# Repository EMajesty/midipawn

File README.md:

# midipawn

MIDI-controlled relay switcher built on the Raspberry Pi Pico (RP2040). Accepts MIDI over USB and TRS (GPIO 9). Controls 10 bypass relays via GPIO 10-19.

## MIDI interface

The device accepts messages on both USB MIDI and serial MIDI (TRS input on GPIO 9). Default MIDI channel is **6**.

### Relay control

Relay states are set via two CC messages. Each CC value is a 5-bit bitmask where bit 0 is the lowest-numbered relay in the group.

| CC  | Bit 0 | Bit 1 | Bit 2 | Bit 3 | Bit 4 |
|-----|-------|-------|-------|-------|-------|
| 80  | Relay 1 (GPIO 10) | Relay 2 (GPIO 11) | Relay 3 (GPIO 12) | Relay 4 (GPIO 13) | Relay 5 (GPIO 14) |
| 81  | Relay 6 (GPIO 15) | Relay 7 (GPIO 16) | Relay 8 (GPIO 17) | Relay 9 (GPIO 18) | Relay 10 (GPIO 19) |

Example: sending CC 80 with value `0x15` (binary `10101`) activates relays 1, 3, 5 and deactivates relays 2, 4.

### Channel configuration

The MIDI channel is configurable via SysEx over USB and persists across power cycles (stored in flash).

```
F0 7D 01 <channel> F7
```

`<channel>` is `0x00`-`0x0F` for MIDI channels 1-16.

Example: `F0 7D 01 05 F7` sets the device to channel 6 (the default).

## Building

Requires [PlatformIO](https://platformio.org/).

```
cd firmware
pio run
```

## Flashing

Hold the BOOTSEL button on the Pico while plugging in USB, then:

```
cd firmware
pio run -t upload
```

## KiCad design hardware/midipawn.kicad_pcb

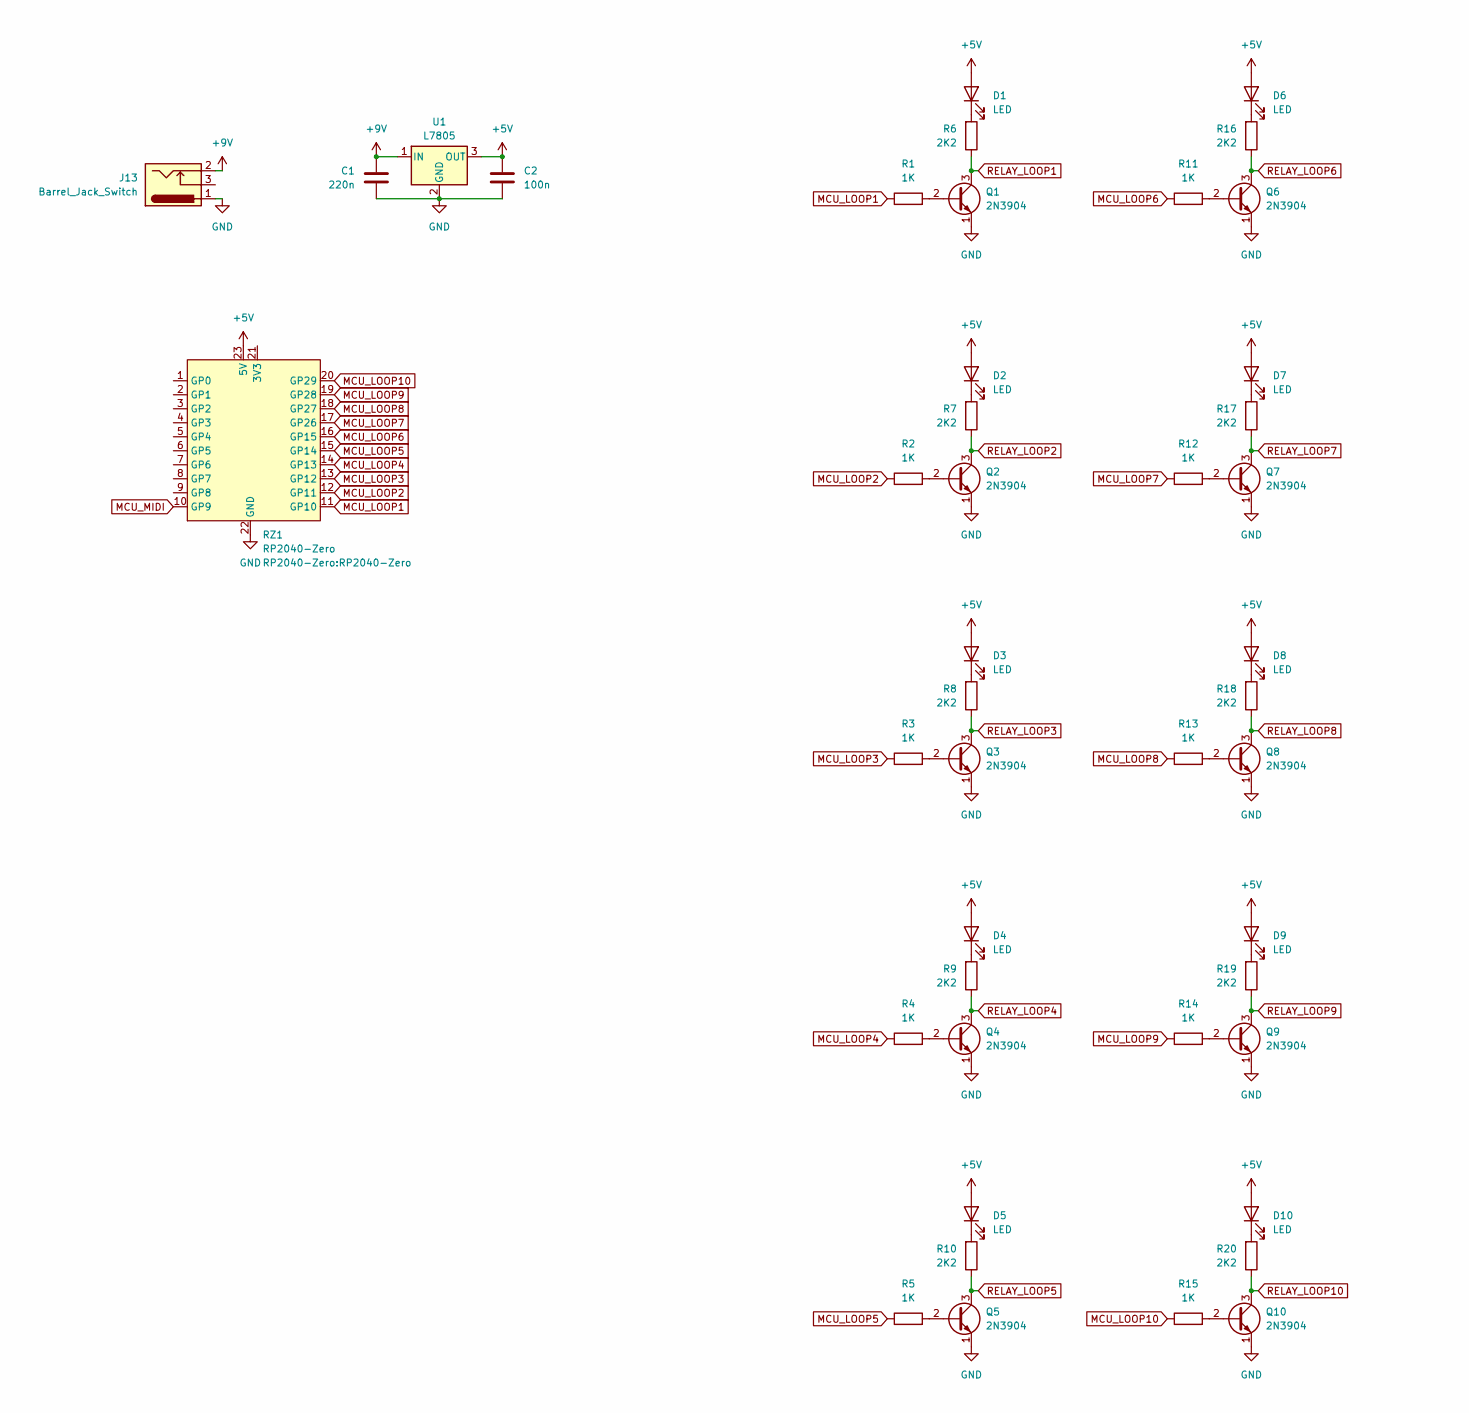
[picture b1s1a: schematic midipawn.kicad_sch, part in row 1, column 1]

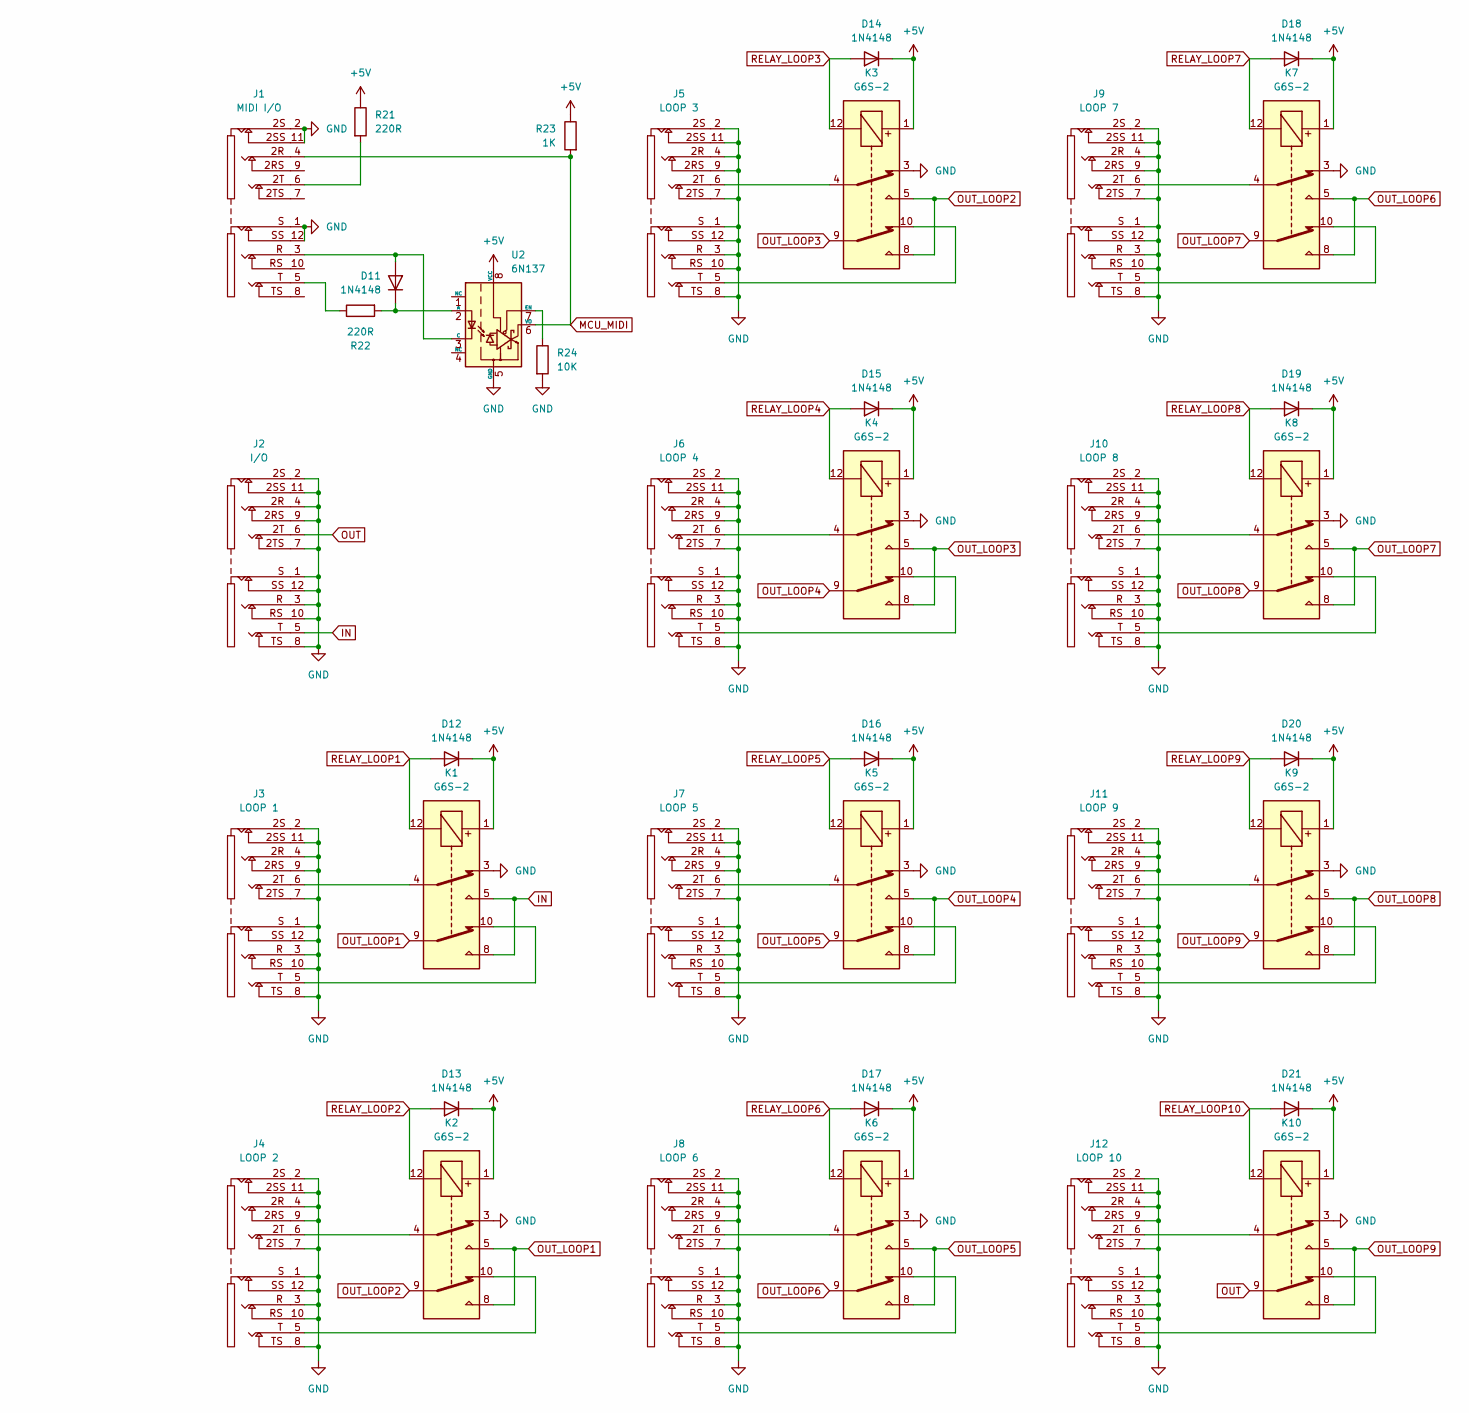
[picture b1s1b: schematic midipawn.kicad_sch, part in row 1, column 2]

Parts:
C1: 220n; C_Rect_L7.0mm_W4.5mm_P5.00mm
C2: 100n; C_Rect_L7.0mm_W2.5mm_P5.00mm
D1, D2, D3, D4, D5, D6, D7, D8, D9, D10: LED; LED_D3.0mm
D11, D12, D13, D14, D15, D16, D17, D18, D19, D20, D21: 1N4148; D_DO-35_SOD27_P7.62mm_Horizontal
J1: MIDI I/O; CK635-037
J2: I/O; CK635-037
J3: LOOP 1; CK635-037
J4: LOOP 2; CK635-037
J5: LOOP 3; CK635-037
J6: LOOP 4; CK635-037
J7: LOOP 5; CK635-037
J8: LOOP 6; CK635-037
J9: LOOP 7; CK635-037
J10: LOOP 8; CK635-037
J11: LOOP 9; CK635-037
J12: LOOP 10; CK635-037
J13: Barrel_Jack_Switch; BarrelJack_Horizontal
K1, K2, K3, K4, K5, K6, K7, K8, K9, K10: G6S-2; Relay_DPDT_Omron_G6S-2
Q1, Q2, Q3, Q4, Q5, Q6, Q7, Q8, Q9, Q10: 2N3904; TO-92_Inline_Wide
R1, R2, R3, R4, R5, R11, R12, R13, R14, R15, R23: 1K; R_Axial_DIN0204_L3.6mm_D1.6mm_P7.62mm_Horizontal
R6, R7, R8, R9, R10, R16, R17, R18, R19, R20: 2K2; R_Axial_DIN0204_L3.6mm_D1.6mm_P7.62mm_Horizontal
R21, R22: 220R; R_Axial_DIN0204_L3.6mm_D1.6mm_P7.62mm_Horizontal
R24: 10K; R_Axial_DIN0204_L3.6mm_D1.6mm_P7.62mm_Horizontal
RZ1: RP2040-Zero
U1: L7805; TO-220-3_Vertical
U2: 6N137; DIP-8_W7.62mm

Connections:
+5V: C2.1, D1.2 (A), D2.2 (A), D3.2 (A), D4.2 (A), D5.2 (A), D6.2 (A), D7.2 (A), D8.2 (A), D9.2 (A), D10.2 (A), D12.1 (K), D13.1 (K), D14.1 (K), D15.1 (K), D16.1 (K), D17.1 (K), D18.1 (K), D19.1 (K), D20.1 (K), D21.1 (K), K1.1, K2.1, K3.1, K4.1, K5.1, K6.1, K7.1, K8.1, K9.1, K10.1, R21.1, R23.1, RZ1.23 (5V), U1.3 (OUT), U2.8 (VCC)
+9V: C1.1, J13.2, U1.1 (IN)
GND: C1.2, C2.2, J1.1 (S), J1.2 (2S), J1.11 (2SS), J1.12 (SS), J2.1 (S), J2.2 (2S), J2.3 (R), J2.4 (2R), J2.7 (2TS), J2.8 (TS), J2.9 (2RS), J2.10 (RS), J2.11 (2SS), J2.12 (SS), J3.1 (S), J3.2 (2S), J3.3 (R), J3.4 (2R), J3.7 (2TS), J3.8 (TS), J3.9 (2RS), J3.10 (RS), J3.11 (2SS), J3.12 (SS), J4.1 (S), J4.2 (2S), J4.3 (R), J4.4 (2R), J4.7 (2TS), J4.8 (TS), J4.9 (2RS), J4.10 (RS), J4.11 (2SS), J4.12 (SS), J5.1 (S), J5.2 (2S), J5.3 (R), J5.4 (2R), J5.7 (2TS), J5.8 (TS), J5.9 (2RS), J5.10 (RS), J5.11 (2SS), J5.12 (SS), J6.1 (S), J6.2 (2S), J6.3 (R), J6.4 (2R), J6.7 (2TS), J6.8 (TS), J6.9 (2RS), J6.10 (RS), J6.11 (2SS), J6.12 (SS), J7.1 (S), J7.2 (2S), J7.3 (R), J7.4 (2R), J7.7 (2TS), J7.8 (TS), J7.9 (2RS), J7.10 (RS), J7.11 (2SS), J7.12 (SS), J8.1 (S), J8.2 (2S), J8.3 (R), J8.4 (2R), J8.7 (2TS), J8.8 (TS), J8.9 (2RS), J8.10 (RS), J8.11 (2SS), J8.12 (SS), J9.1 (S), J9.2 (2S), J9.3 (R), J9.4 (2R), J9.7 (2TS), J9.8 (TS), J9.9 (2RS), J9.10 (RS), J9.11 (2SS), J9.12 (SS), J10.1 (S), J10.2 (2S), J10.3 (R), J10.4 (2R), J10.7 (2TS), J10.8 (TS), J10.9 (2RS), J10.10 (RS), J10.11 (2SS), J10.12 (SS), J11.1 (S), J11.2 (2S), J11.3 (R), J11.4 (2R), J11.7 (2TS), J11.8 (TS), J11.9 (2RS), J11.10 (RS), J11.11 (2SS), J11.12 (SS), J12.1 (S), J12.2 (2S), J12.3 (R), J12.4 (2R), J12.7 (2TS), J12.8 (TS), J12.9 (2RS), J12.10 (RS), J12.11 (2SS), J12.12 (SS), J13.1, K1.3, K2.3, K3.3, K4.3, K5.3, K6.3, K7.3, K8.3, K9.3, K10.3, Q1.1 (E), Q2.1 (E), Q3.1 (E), Q4.1 (E), Q5.1 (E), Q6.1 (E), Q7.1 (E), Q8.1 (E), Q9.1 (E), Q10.1 (E), R24.2, RZ1.22 (GND), U1.2 (GND), U2.5 (GND)
IN: J2.5 (T), K1.5, K1.8
MCU_LOOP1: R1.1, RZ1.11 (GP10)
MCU_LOOP2: R2.1, RZ1.12 (GP11)
MCU_LOOP3: R3.1, RZ1.13 (GP12)
MCU_LOOP4: R4.1, RZ1.14 (GP13)
MCU_LOOP5: R5.1, RZ1.15 (GP14)
MCU_LOOP6: R11.1, RZ1.16 (GP15)
MCU_LOOP7: R12.1, RZ1.17 (GP26)
MCU_LOOP8: R13.1, RZ1.18 (GP27)
MCU_LOOP9: R14.1, RZ1.19 (GP28)
MCU_LOOP10: R15.1, RZ1.20 (GP29)
MCU_MIDI: J1.4 (2R), R23.2, RZ1.10 (GP9), U2.6 (VO)
unnamed: D1.1 (K), R6.2
unnamed: D2.1 (K), R7.2
unnamed: D3.1 (K), R8.2
unnamed: D4.1 (K), R9.2
unnamed: D5.1 (K), R10.2
unnamed: D6.1 (K), R16.2
unnamed: D7.1 (K), R17.2
unnamed: D8.1 (K), R18.2
unnamed: D9.1 (K), R19.2
unnamed: D10.1 (K), R20.2
unnamed: D11.2 (A), J1.3 (R), U2.3 (C)
unnamed: D11.1 (K), R22.2, U2.2 (A)
unnamed: J1.6 (2T), R21.2
unnamed: J1.5 (T), R22.1
unnamed: J3.6 (2T), K1.4
unnamed: J3.5 (T), K1.10
unnamed: J4.6 (2T), K2.4
unnamed: J4.5 (T), K2.10
unnamed: J5.6 (2T), K3.4
unnamed: J5.5 (T), K3.10
unnamed: J6.6 (2T), K4.4
unnamed: J6.5 (T), K4.10
unnamed: J7.6 (2T), K5.4
unnamed: J7.5 (T), K5.10
unnamed: J8.6 (2T), K6.4
unnamed: J8.5 (T), K6.10
unnamed: J9.6 (2T), K7.4
unnamed: J9.5 (T), K7.10
unnamed: J10.6 (2T), K8.4
unnamed: J10.5 (T), K8.10
unnamed: J11.6 (2T), K9.4
unnamed: J11.5 (T), K9.10
unnamed: J12.6 (2T), K10.4
unnamed: J12.5 (T), K10.10
unnamed: Q1.2 (B), R1.2
unnamed: Q2.2 (B), R2.2
unnamed: Q3.2 (B), R3.2
unnamed: Q4.2 (B), R4.2
unnamed: Q5.2 (B), R5.2
unnamed: Q6.2 (B), R11.2
unnamed: Q7.2 (B), R12.2
unnamed: Q8.2 (B), R13.2
unnamed: Q9.2 (B), R14.2
unnamed: Q10.2 (B), R15.2
unnamed: R24.1, U2.7 (EN)
OUT: J2.6 (2T), K10.9
OUT_LOOP1: K1.9, K2.5, K2.8
OUT_LOOP2: K2.9, K3.5, K3.8
OUT_LOOP3: K3.9, K4.5, K4.8
OUT_LOOP4: K4.9, K5.5, K5.8
OUT_LOOP5: K5.9, K6.5, K6.8
OUT_LOOP6: K6.9, K7.5, K7.8
OUT_LOOP7: K7.9, K8.5, K8.8
OUT_LOOP8: K8.9, K9.5, K9.8
OUT_LOOP9: K9.9, K10.5, K10.8
RELAY_LOOP1: D12.2 (A), K1.12, Q1.3 (C), R6.1
RELAY_LOOP2: D13.2 (A), K2.12, Q2.3 (C), R7.1
RELAY_LOOP3: D14.2 (A), K3.12, Q3.3 (C), R8.1
RELAY_LOOP4: D15.2 (A), K4.12, Q4.3 (C), R9.1
RELAY_LOOP5: D16.2 (A), K5.12, Q5.3 (C), R10.1
RELAY_LOOP6: D17.2 (A), K6.12, Q6.3 (C), R16.1
RELAY_LOOP7: D18.2 (A), K7.12, Q7.3 (C), R17.1
RELAY_LOOP8: D19.2 (A), K8.12, Q8.3 (C), R18.1
RELAY_LOOP9: D20.2 (A), K9.12, Q9.3 (C), R19.1
RELAY_LOOP10: D21.2 (A), K10.12, Q10.3 (C), R20.1

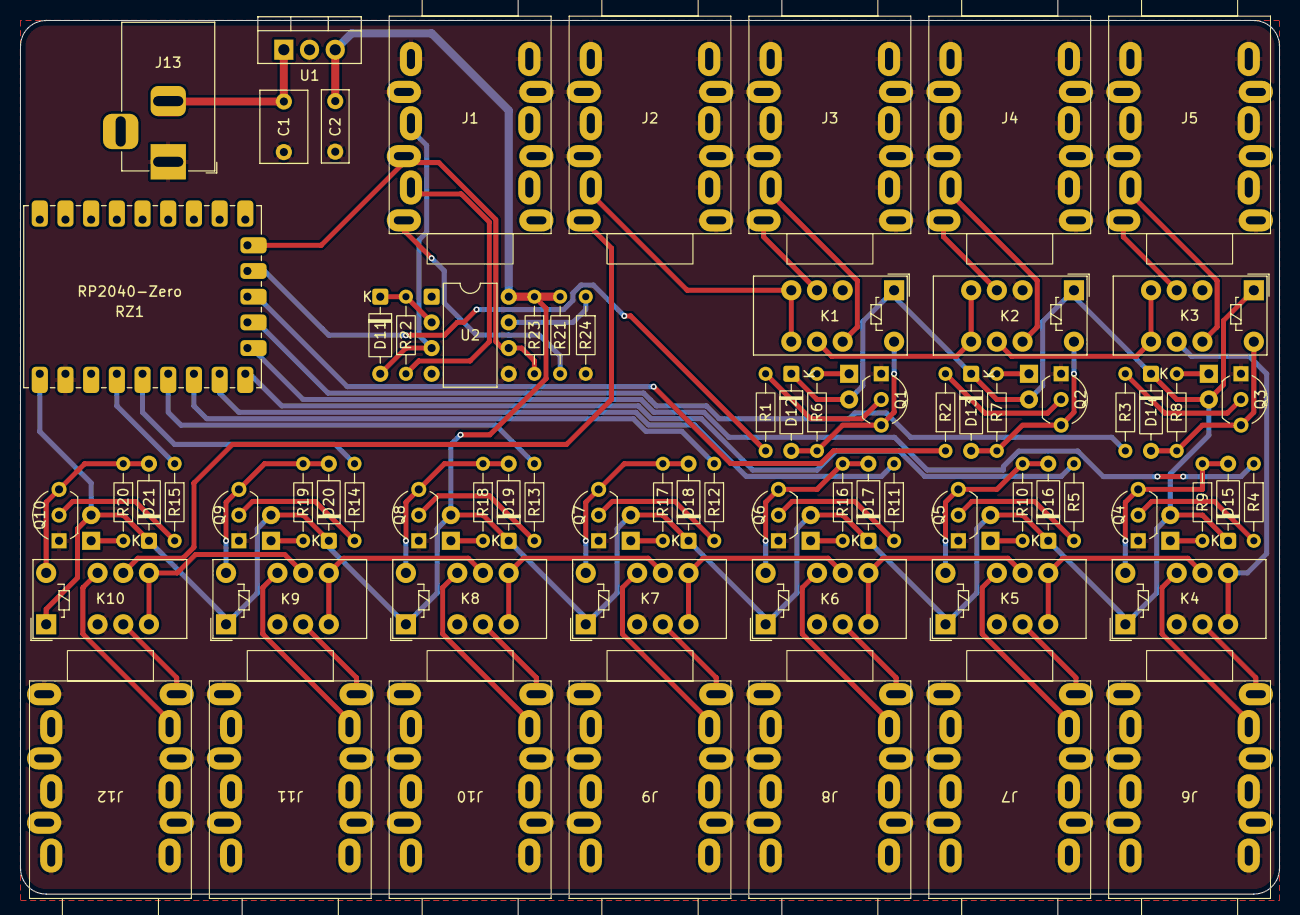
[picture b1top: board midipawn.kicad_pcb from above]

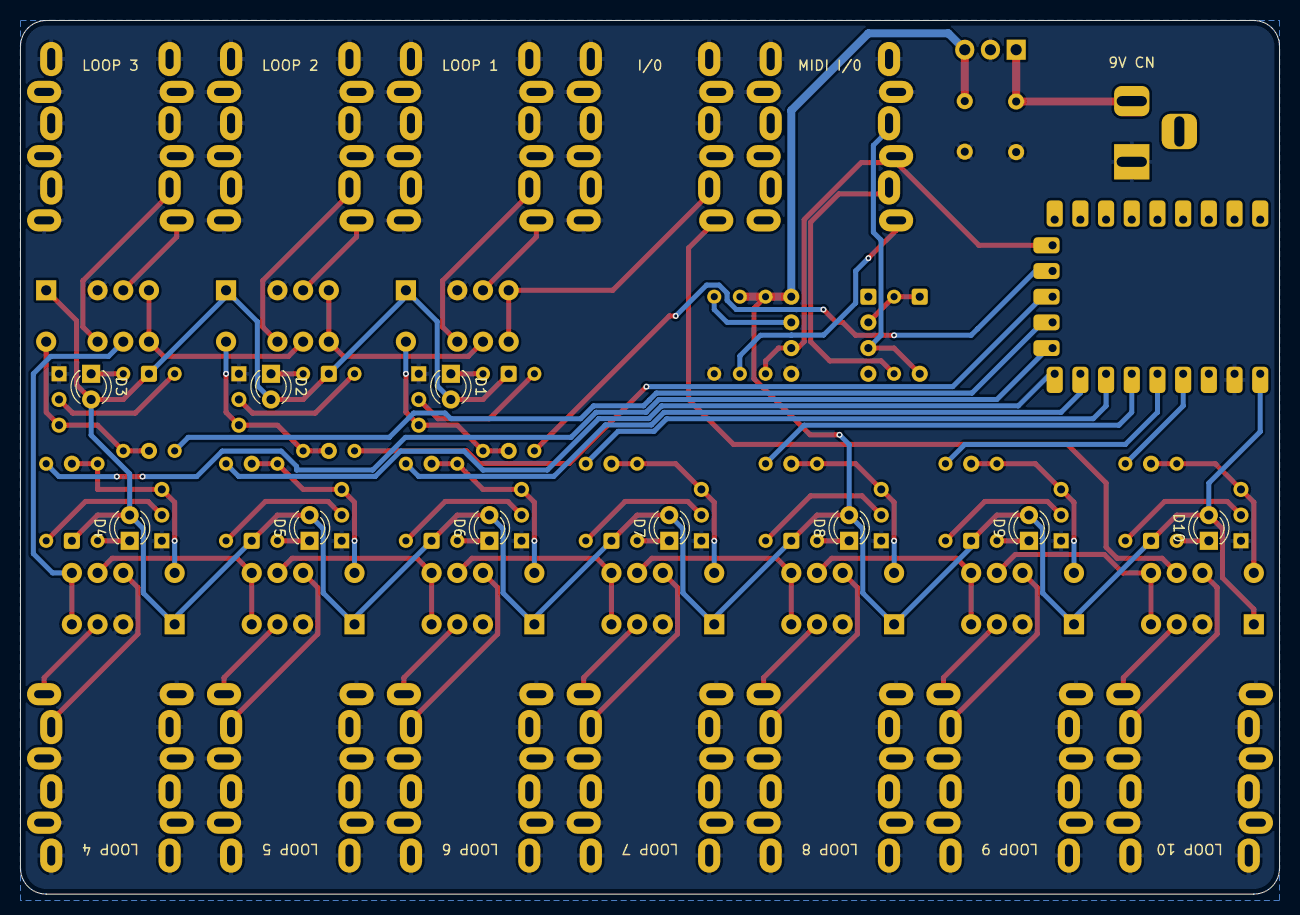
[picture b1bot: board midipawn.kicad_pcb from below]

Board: 2 copper layers, 124.5 x 86.4 mm, 83 parts (10 on the bottom side), 80 nets.

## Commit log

2026-05-29 Prompt is too long
2026-05-29 Add empty README.md
2026-06-04 Add STEP 3D model for audio jacks connector
2026-06-04 Adjust audio jack positions to align with board edge
2026-06-16 Update PCB layout and regenerate Gerber fabrication files
2026-06-29 Add pull-down resistor on voltage regulator enable pin
2026-06-29 Add Nix flake devshell with PlatformIO and firmware scaffold
2026-06-29 Add .gitignore for KiCad, PlatformIO, Nix, and OS artifacts
2026-06-29 Add README with MIDI protocol docs and build instructions
2026-06-29 Remove .direnv from version control
2026-06-29 Replace DIN with TRS for MIDI input connector references
